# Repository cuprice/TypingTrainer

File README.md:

## タイピング練習用キーボード基板 Typing Haptic Trainer (Prototype)

2025.11.25
Githubに公開してから数ヶ月経ちました。それ以来、触覚を利用したタッチタイピングの練習機械が他にもあることを知り、私のウェブ検索が十分でなかったと申し訳なく思いました。他の人々の作る機械はとても複雑でレベルの高いことも知り、私はまだまだ勉強不足であると思いました。もしお嫌でなければ、学習の活動を見守っていただければ幸いです。

I published my project on GitHub a few months ago.
After that, I learned that there are other typing training devices that use touch.
I felt sorry because my web search was not good enough.
I also found that other people’s devices are very complex and high-level, and I realized that I still have a lot to learn. If you don’t mind, I would be happy if you could watch my learning journey.

2025.11.23
基板を新しくしました！作った基板にArduino Nano Everyを組み込みました。
I made a new PCB and installed an Arduino Nano Every on it.

このリポジトリは回路・プログラミング初学者の学習用です。あたたかく見守っていただけると嬉しいです。

これは、プログラミングや回路の初心者である私が、自分なりに学びながら作ってみた実装基板です。  
8つのキーに振動する部品を付け、目で確認しなくてもどこを押せば良いかがわかる機能を目指しました。
公開しようと思ったきっかけは、似たようなアイデアのタイピング練習機を見つけることができなかったためです。

このリポジトリでは、タイピング練習を目的としたキーボード基板の設計データを公開しています。  
基板はKiCad 9.0で設計されています。振動するキー順番を変更するには、Arduinoのスケッチを編集する必要があります。

ただし、現在はアイデア段階であり、完全な完成品ではありません。今後の改善や追加機能に関しては更新を行う予定です。

This repository is for beginners who are learning circuits and programming.
I’d be happy if you could kindly support it.

This is a keyboard I made while learning programming and circuits by myself.
I am still a beginner, but I tried my best to build it.

I added small parts that can vibrate to 8 keys.
This way, you can feel which key to press without looking.

I decided to share this because I couldn't find a similar typing practice device online.

In this repository, I show the design data for this keyboard.
I made the design using KiCad 9.0.
If you want to change the order of the vibrating keys, you need to change the Arduino program.

Please note that this is still just an idea, not a finished product.
I want to improve it and add more features in the future.

---

## 特徴

- 10列、3段のキー(計30個)による練習用構成
- リセットスイッチ付き
- Cherry MX対応
- Arduino nano everyで完璧ではありませんが、一応動作確認済みです (後継機のモデルは動作未確認)
- KiCad 9.0で基板設計
- 基板サイズ：約261.1mm × 81.5mm
- 電源：Arduino nano every経由でのUSB給電

This is a practice keyboard layout with 30 keys, arranged in 10 columns and 3 rows.
It includes a reset switch. It's compatible with Cherry MX switches. I've confirmed it works with the Arduino nano every, although it's not perfect. I haven't tested it with newer Arduino models. The circuit board was designed using KiCad 9.0. The board size is about 261.1mm × 81.5mm, and it's powered by USB through the Arduino nano every.

どの段のキーを押せば良いかを、3段階のブザー音で教えるためのコードを加筆修正しました。上の段ならば3回鳴り、下の段ならば１回鳴り、真ん中の段なら２回鳴るという仕組みにしました。振動モーターがないキーの場合は、振動する長さを変えて位置を知らせるようにしました。

I changed the code to use three kinds of buzzer sounds to tell the user which row of keys to press.
If the key is on the top row, the buzzer beeps three times.
If the key is on the bottom row, it beeps one time.
If the key is on the middle row, it beeps two times.
For keys that do not have a vibration motor, the device changes the length of the vibration to show the position.

---

## ファイル構成

~~~

TypingTrainer/
    ├── TYPING-TRAINER-V5-2025-10-13_115341/ # KiCad設計ファイル
    ├── TYPING-TRAINER-V5.1.zip # ガーバーデータ（基板製造用）
    ├── TrainerV5active/ # Arduinoスケッチ
    ├── images/ # 写真・完成図
    ├── docs/ # 部品表
    └── README.md # このファイル

~~~

---

## 完成イメージ、回路図、動作の様子

[動作の様子](images/working.mp4)

[モーターの動き](images/shaker.mp4)

---

## 使い方
1. ガーバーファイルをPCBwayなどで製造依頼
2. 回路図などを見ながら部品を実装
3. Arduino nano everyをUSBケーブルでPCと接続
4. PCからArduinoへ、ファームウェアを書き込み

---

## 必要部品

| Value               | Reference      | Qty | 備考                                           | 画像 |
|---------------------|----------------|-----|------------------------------------------------|------|
| Arduino Nano Every  | A1             | 1   | マイクロコントローラー（ソケットピン経由で実装） |  |
| Buzzer              | BZ1            | 1   | ブザー                                         |  |
| 1N4148              | D1 〜 D30      | 30  | スイッチのマトリックス用ダイオード             |  |
| LED                 | D100, D101     | 2   | インジケーターLED                              |  |
| Motor DC            | M1 〜 M8       | 8   | DCモーター                                     |  |
| 10k                 | R1 〜 R12      | 12  | 抵抗（10kΩ）                                   |  |
| 330                 | R13, R14       | 2   | 抵抗（330Ω, LED電流制限用）                    |  |
| Cherry MX Switch    | SW1 〜 SW30    | 30  | Cherry MX互換キースイッチ(キーキャップはお好みで)                      |  |
| 2pin Button         | SW100, SW101   | 2   | 2ピンのタクトスイッチなど                      |  |
| MCP23017_SP         | U2             | 1   | I/Oエキスパンダー（ICソケットの上に実装）      |  |

---

## KiCad情報

- KiCad バージョン: 9.0
- 古いバージョンでは一部ファイルが開けない可能性があります。
- 最新バージョンでの動作は未確認です。

---

## ライセンス

この基板デザインは MIT ライセンスで公開しています。  

---

## よくある質問

準備中
**Q. ？**  
A. 

---

## 注意事項

- 初心者が学びながら作ったものなので、不完全な点もあるかもしれません。
- Arduinoスケッチの一部のコード作成に、生成AI（ChatGPT）を補助的に活用しました。

---

## Special Thanks

- ネット上のチュートリアルや電子工作記事の皆さま

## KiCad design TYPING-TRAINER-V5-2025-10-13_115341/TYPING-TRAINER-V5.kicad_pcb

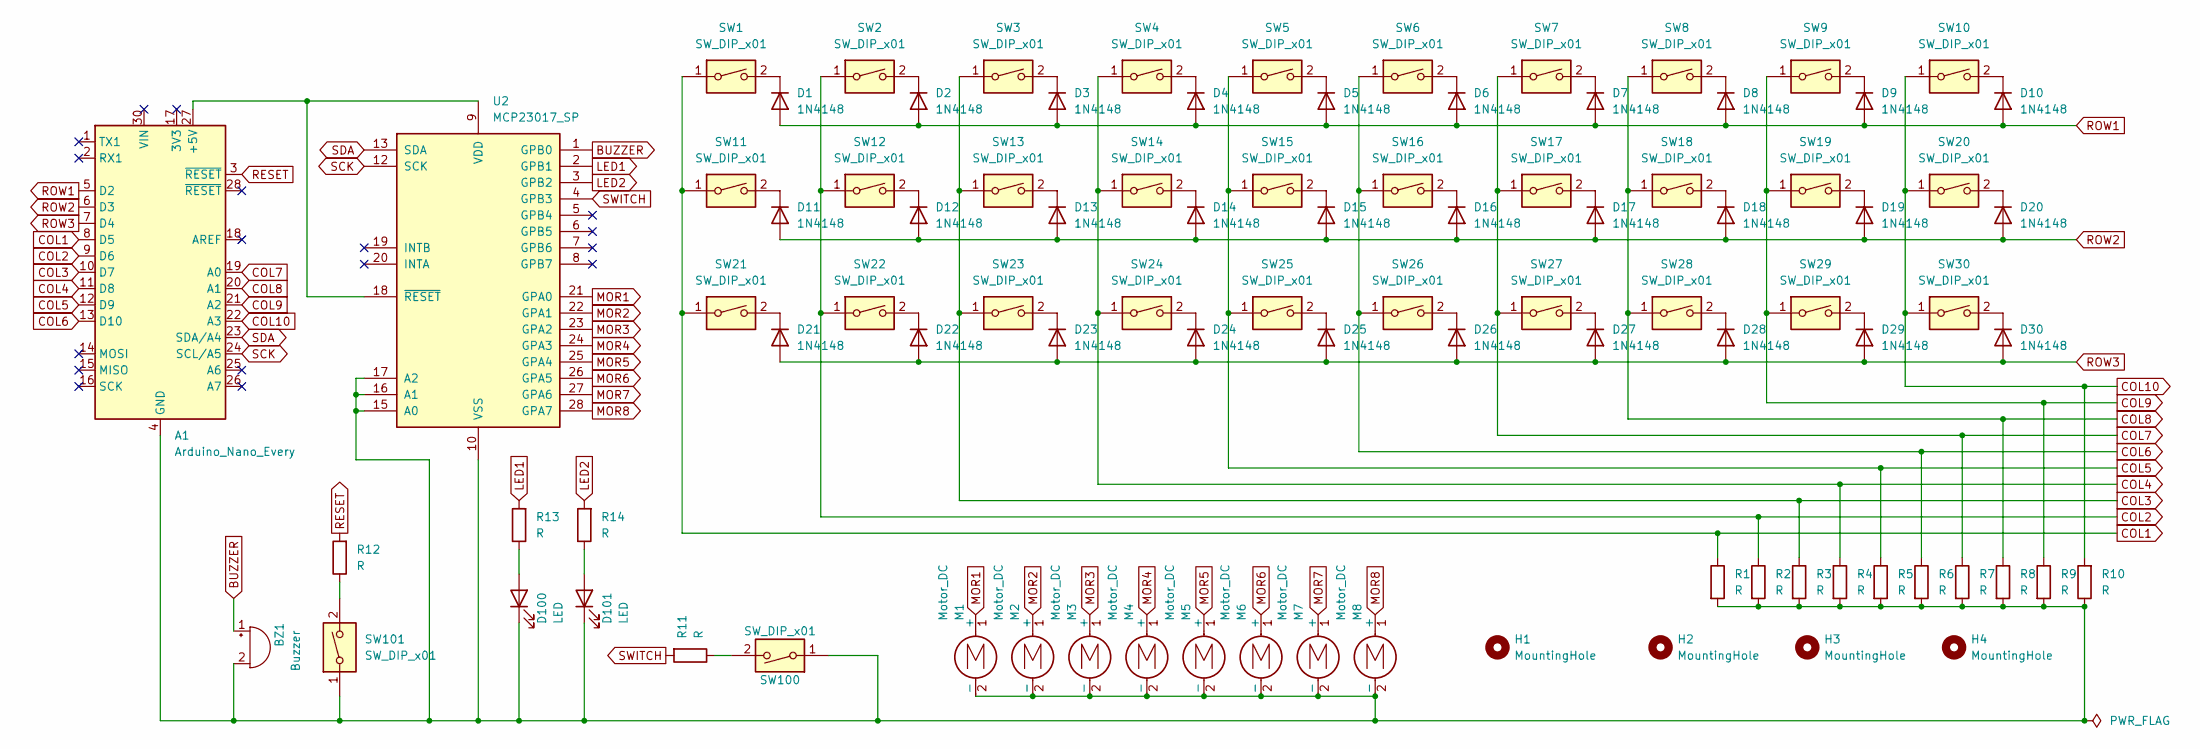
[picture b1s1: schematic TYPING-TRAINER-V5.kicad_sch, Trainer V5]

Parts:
A1: Arduino_Nano_Every; Arduino_Nano
BZ1: Buzzer; Buzzer_TDK_PS1240P02BT_D12.2mm_H6.5mm
D1, D2, D3, D4, D5, D6, D7, D8, D9, D10, D11, D12, D13, D14, D15, D16, D17, D18, D19, D20, D21, D22, D23, D24, D25, D26, D27, D28, D29, D30: 1N4148; D_DO-35_SOD27_P7.62mm_Horizontal-b
D100, D101: LED; LED_D5.0mm_FlatTop
H1, H2, H3, H4: MountingHole; MountingHole_3.2mm_M3
M1, M2, M3, M4, M5, M6, M7, M8: Motor_DC; PinHeader_1x02_P2.54mm_Vertical
R1, R2, R3, R4, R5, R6, R7, R8, R9, R10, R11, R12, R13, R14: R; R_Axial_DIN0207_L6.3mm_D2.5mm_P10.16mm_Horizontal
SW1, SW2, SW3, SW4, SW5, SW6, SW7, SW8, SW9, SW10, SW11, SW12, SW13, SW14, SW15, SW16, SW17, SW18, SW19, SW20, SW21, SW22, SW23, SW24, SW25, SW26, SW27, SW28, SW29, SW30: SW_DIP_x01; SW_Cherry_MX_1.00u_PCB
SW100, SW101: SW_DIP_x01; SW_PUSH_1P1T_6x3.5mm_H4.3_APEM_MJTP1243
U2: MCP23017_SP; DIP-28_W7.62mm

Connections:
BUZZER: BZ1.1 (+), U2.1 (GPB0)
COL1: A1.8 (D5), R1.1, SW1.1, SW11.1, SW21.1
COL2: A1.9 (D6), R2.1, SW2.1, SW12.1, SW22.1
COL3: A1.10 (D7), R3.1, SW3.1, SW13.1, SW23.1
COL4: A1.11 (D8), R4.1, SW4.1, SW14.1, SW24.1
COL5: A1.12 (D9), R5.1, SW5.1, SW15.1, SW25.1
COL6: A1.13 (D10), R6.1, SW6.1, SW16.1, SW26.1
COL7: A1.19 (A0), R7.1, SW7.1, SW17.1, SW27.1
COL8: A1.20 (A1), R8.1, SW8.1, SW18.1, SW28.1
COL9: A1.21 (A2), R9.1, SW9.1, SW19.1, SW29.1
COL10: A1.22 (A3), R10.2, SW10.1, SW20.1, SW30.1
LED1: R13.2, U2.2 (GPB1)
LED2: R14.2, U2.3 (GPB2)
MOR1: M1.1 (+), U2.21 (GPA0)
MOR2: M2.1 (+), U2.22 (GPA1)
MOR3: M3.1 (+), U2.23 (GPA2)
MOR4: M4.1 (+), U2.24 (GPA3)
MOR5: M5.1 (+), U2.25 (GPA4)
MOR6: M6.1 (+), U2.26 (GPA5)
MOR7: M7.1 (+), U2.27 (GPA6)
MOR8: M8.1 (+), U2.28 (GPA7)
unnamed: A1.27 (+5V), U2.9 (VDD), U2.18 (~RESET)
unnamed: A1.4 (GND), A1.29 (GND), BZ1.2 (-), D100.1 (K), D101.1 (K), M1.2 (-), M2.2 (-), M3.2 (-), M4.2 (-), M5.2 (-), M6.2 (-), M7.2 (-), M8.2 (-), R1.2, R2.2, R3.2, R4.2, R5.2, R6.2, R7.2, R8.2, R9.2, R10.1, SW100.1, SW101.1, U2.10 (VSS), U2.15 (A0), U2.16 (A1), U2.17 (A2)
unnamed: D1.1 (K), SW1.2
unnamed: D2.1 (K), SW2.2
unnamed: D3.1 (K), SW3.2
unnamed: D4.1 (K), SW4.2
unnamed: D5.1 (K), SW5.2
unnamed: D6.1 (K), SW6.2
unnamed: D7.1 (K), SW7.2
unnamed: D8.1 (K), SW8.2
unnamed: D9.1 (K), SW9.2
unnamed: D10.1 (K), SW10.2
unnamed: D11.1 (K), SW11.2
unnamed: D12.1 (K), SW12.2
unnamed: D13.1 (K), SW13.2
unnamed: D14.1 (K), SW14.2
unnamed: D15.1 (K), SW15.2
unnamed: D16.1 (K), SW16.2
unnamed: D17.1 (K), SW17.2
unnamed: D18.1 (K), SW18.2
unnamed: D19.1 (K), SW19.2
unnamed: D20.1 (K), SW20.2
unnamed: D21.1 (K), SW21.2
unnamed: D22.1 (K), SW22.2
unnamed: D23.1 (K), SW23.2
unnamed: D24.1 (K), SW24.2
unnamed: D25.1 (K), SW25.2
unnamed: D26.1 (K), SW26.2
unnamed: D27.1 (K), SW27.2
unnamed: D28.1 (K), SW28.2
unnamed: D29.1 (K), SW29.2
unnamed: D30.1 (K), SW30.2
unnamed: D100.2 (A), R13.1
unnamed: D101.2 (A), R14.1
unnamed: R11.1, SW100.2
unnamed: R12.1, SW101.2
RESET: A1.3 (~RESET), R12.2
ROW1: A1.5 (D2), D1.2 (A), D2.2 (A), D3.2 (A), D4.2 (A), D5.2 (A), D6.2 (A), D7.2 (A), D8.2 (A), D9.2 (A), D10.2 (A)
ROW2: A1.6 (D3), D11.2 (A), D12.2 (A), D13.2 (A), D14.2 (A), D15.2 (A), D16.2 (A), D17.2 (A), D18.2 (A), D19.2 (A), D20.2 (A)
ROW3: A1.7 (D4), D21.2 (A), D22.2 (A), D23.2 (A), D24.2 (A), D25.2 (A), D26.2 (A), D27.2 (A), D28.2 (A), D29.2 (A), D30.2 (A)
SCK: A1.24 (SCL/A5), U2.12 (SCK)
SDA: A1.23 (SDA/A4), U2.13 (SDA)
SWITCH: R11.2, U2.4 (GPB3)

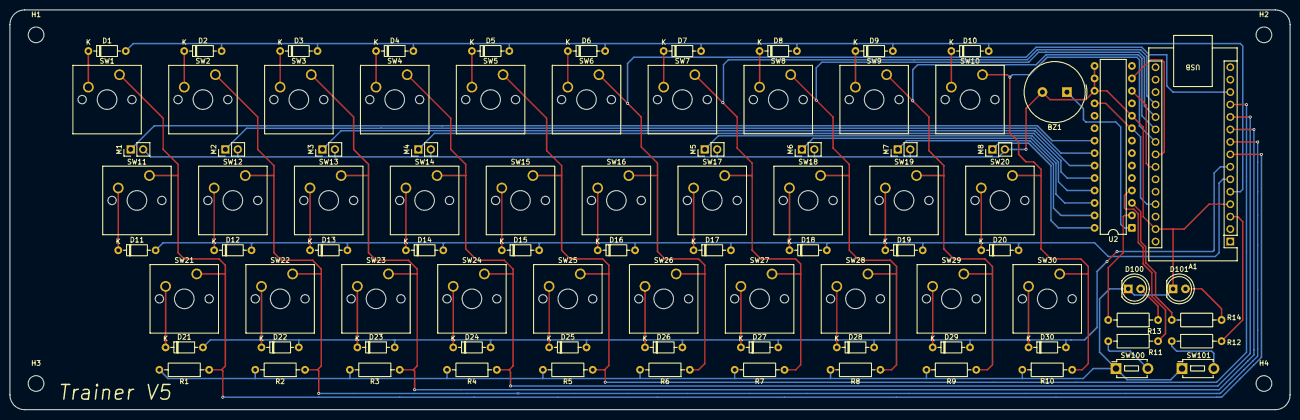
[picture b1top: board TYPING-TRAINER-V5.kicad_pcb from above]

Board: 2 copper layers, 261.1 x 81.5 mm, 93 parts (0 on the bottom side), 64 nets.

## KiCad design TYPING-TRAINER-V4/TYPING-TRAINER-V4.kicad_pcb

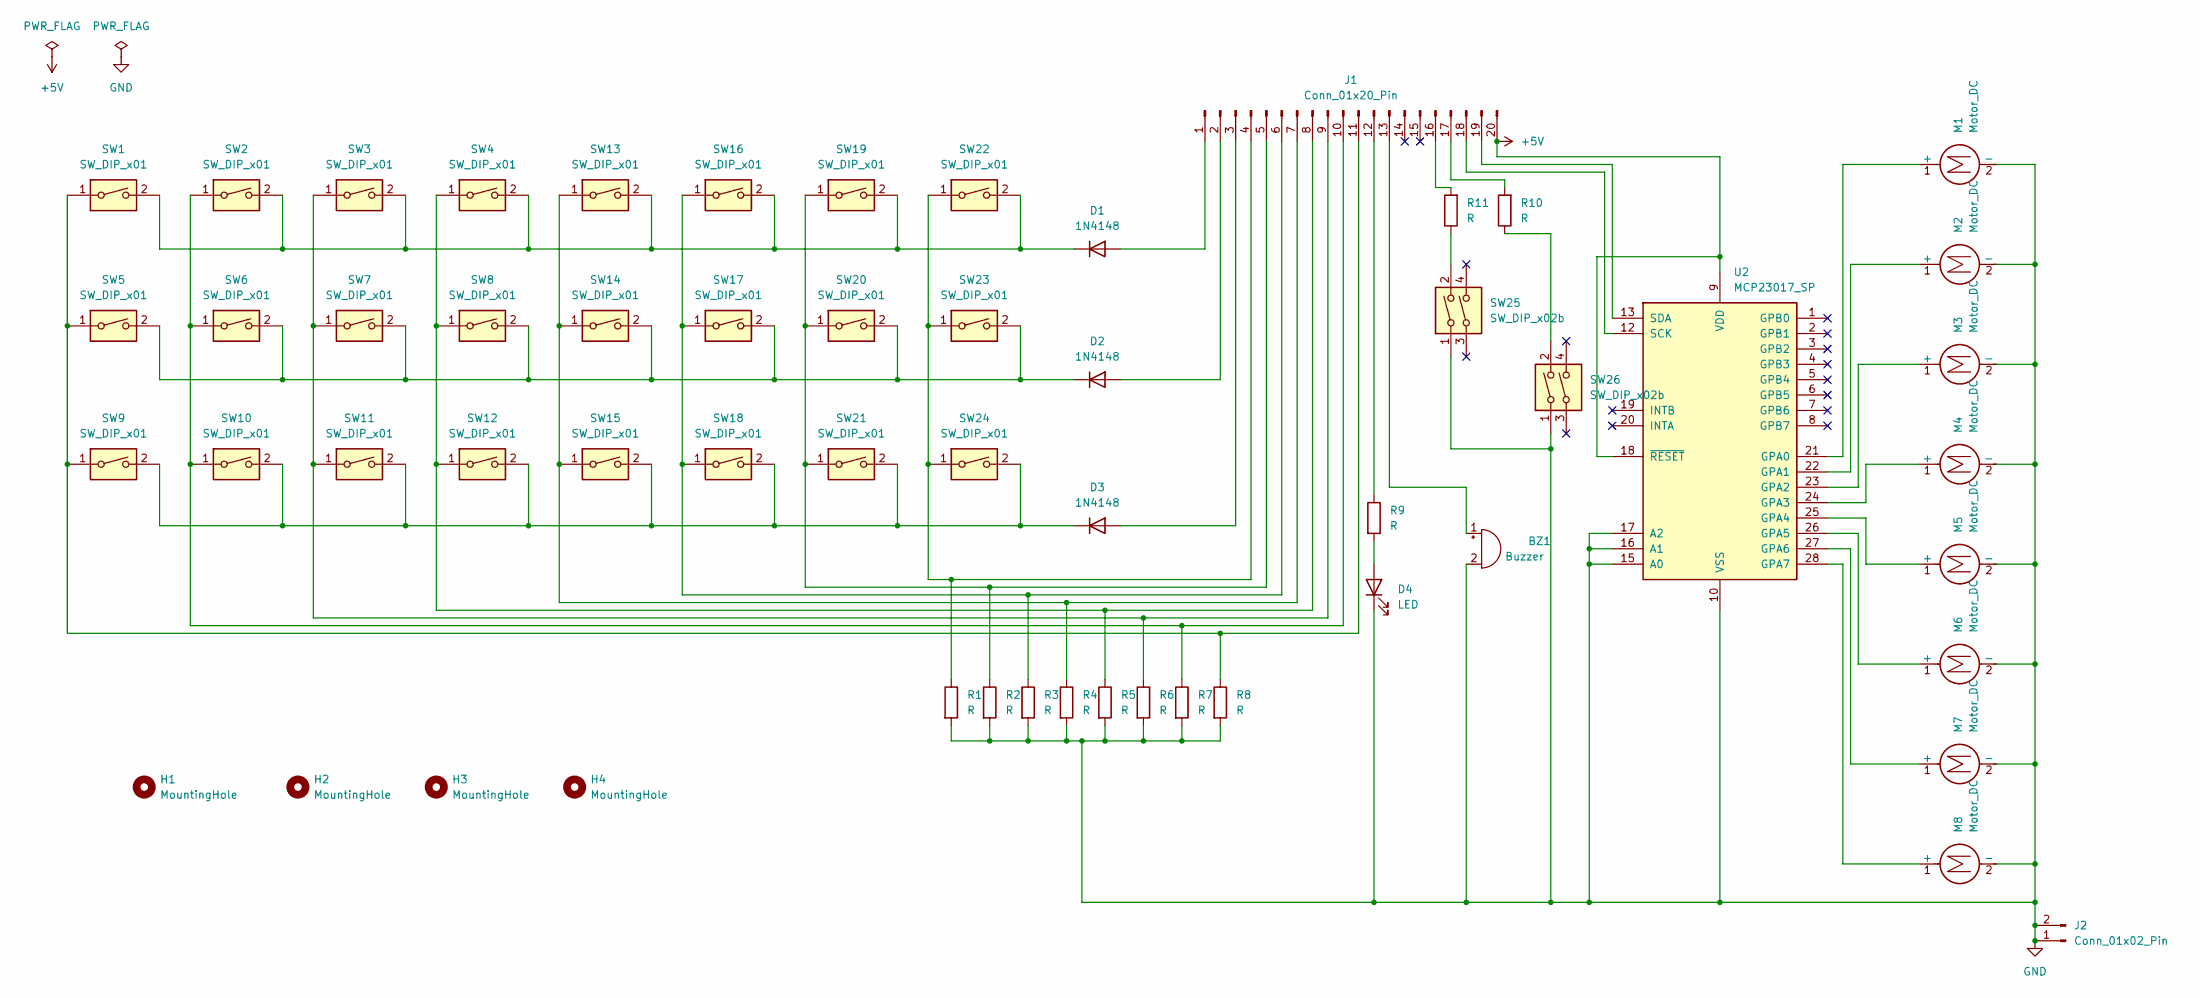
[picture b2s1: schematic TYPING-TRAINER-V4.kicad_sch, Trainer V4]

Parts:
BZ1: Buzzer; XDCR_CMT-9648-85T
D1, D2, D3: 1N4148; D_DO-35_SOD27_P7.62mm_Horizontal
D4: LED; LED_D5.0mm_FlatTop
H1, H2, H3, H4: MountingHole; MountingHole_3.2mm_M3
J1: Conn_01x20_Pin; PinHeader_1x20_P2.54mm_Vertical
J2: Conn_01x02_Pin; PinHeader_1x02_P2.54mm_Vertical
M1, M2, M3, M4, M5, M6, M7, M8: Motor_DC; PinHeader_1x02_P2.54mm_Vertical
R1, R2, R3, R4, R5, R6, R7, R8, R9, R10, R11: R; R_Axial_DIN0207_L6.3mm_D2.5mm_P10.16mm_Horizontal
SW1, SW2, SW3, SW4, SW5, SW6, SW7, SW8, SW9, SW10, SW11, SW12, SW13, SW14, SW15, SW16, SW17, SW18, SW19, SW20, SW21, SW22, SW23, SW24: SW_DIP_x01; SW_Cherry_MX_1.00u_PCB
SW25, SW26: SW_DIP_x02b; SW_PUSH_6mm
U2: MCP23017_SP; DIP-28_W7.62mm

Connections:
+5V: J1.20, U2.9 (VDD), U2.18 (~RESET)
GND: BZ1.2 (-), D4.1 (K), J2.1, J2.2, M1.2 (-), M2.2 (-), M3.2 (-), M4.2 (-), M5.2 (-), M6.2 (-), M7.2 (-), M8.2 (-), R1.2, R2.2, R3.2, R4.2, R5.2, R6.2, R7.2, R8.2, SW25.1, SW26.1, U2.10 (VSS), U2.15 (A0), U2.16 (A1), U2.17 (A2)
unnamed: BZ1.1 (+), J1.13
unnamed: D1.2 (A), J1.1
unnamed: D1.1 (K), SW1.2, SW2.2, SW3.2, SW4.2, SW13.2, SW16.2, SW19.2, SW22.2
unnamed: D2.2 (A), J1.2
unnamed: D2.1 (K), SW5.2, SW6.2, SW7.2, SW8.2, SW14.2, SW17.2, SW20.2, SW23.2
unnamed: D3.2 (A), J1.3
unnamed: D3.1 (K), SW9.2, SW10.2, SW11.2, SW12.2, SW15.2, SW18.2, SW21.2, SW24.2
unnamed: D4.2 (A), R9.2
unnamed: J1.4, R1.1, SW22.1, SW23.1, SW24.1
unnamed: J1.5, R2.1, SW19.1, SW20.1, SW21.1
unnamed: J1.6, R3.1, SW16.1, SW17.1, SW18.1
unnamed: J1.7, R4.1, SW13.1, SW14.1, SW15.1
unnamed: J1.8, R5.1, SW4.1, SW8.1, SW12.1
unnamed: J1.9, R6.1, SW3.1, SW7.1, SW11.1
unnamed: J1.10, R7.1, SW2.1, SW6.1, SW10.1
unnamed: J1.11, R8.1, SW1.1, SW5.1, SW9.1
unnamed: J1.12, R9.1
unnamed: J1.16, R11.2
unnamed: J1.17, R10.2
unnamed: J1.18, U2.12 (SCK)
unnamed: J1.19, U2.13 (SDA)
unnamed: M1.1 (+), U2.21 (GPA0)
unnamed: M2.1 (+), U2.22 (GPA1)
unnamed: M3.1 (+), U2.23 (GPA2)
unnamed: M4.1 (+), U2.24 (GPA3)
unnamed: M5.1 (+), U2.25 (GPA4)
unnamed: M6.1 (+), U2.26 (GPA5)
unnamed: M7.1 (+), U2.27 (GPA6)
unnamed: M8.1 (+), U2.28 (GPA7)
unnamed: R10.1, SW26.2
unnamed: R11.1, SW25.2

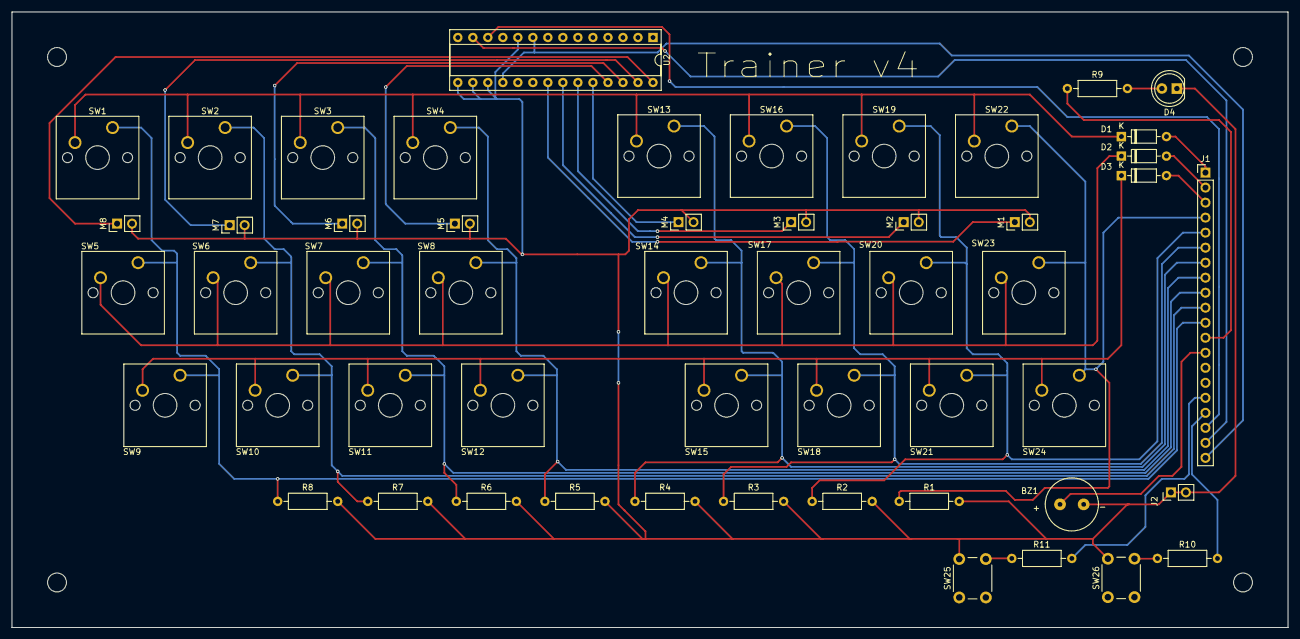
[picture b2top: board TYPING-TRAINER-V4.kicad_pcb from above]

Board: 2 copper layers, 215.9 x 104.1 mm, 57 parts (0 on the bottom side), 33 nets.

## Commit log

2025-06-28 2nd commit
2025-07-01 3rd commit
2025-07-03 Add ignore
2025-07-05 Edit README
2025-07-27 4th commit
2025-08-02 5th commit
2025-08-09 6th commit
2025-08-31 add image
2025-11-23 upgrade to v5
2025-11-25 2025.11.25 readme update
